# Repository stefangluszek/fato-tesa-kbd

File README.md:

# Fat-o-tesa - v0.2

## Introduction
This repository documents my attempt at building a custom mechanical keyboard. I have been considering switching to a split ergonomic keyboard such as the [Ergodox](https://ergodox-ez.com/) for a while now.
I hesitated, mostly because I love my current Varmillo Mechanical keyboard and I was not sure if switching back and forth between the two would be a good idea. At the end I decided it was more about learning the process of building a custom keyboard than actually using it. So I decided to design and build my own custom mechanical keyboard.

The requirements I had were simple, a split mechanical keyboard with the base layout as close to the ISO layout as possible to make switching back and forth as painless as possible. Why ISO? Because I use a Swedish/Norwegian keyboard which uses the ISO layout.

## The layout
I used the [Keyboard Layout Editor](http://www.keyboard-layout-editor.com/) to create the layout. It's based on the ISO 60% preset, but includes the top row with a couple of functional keys. I will explain why I needed the top row later on when we get to the PCB design.

The raw layout can be found [here](layouts/layout.kle).

## version v0.2
This is my second attempt at designing the PCBs. The [first version](README.v0.1.md) was a good learning experience but it had some major flaws that are addressed in this version.

## PCB design
The PCB is designed in KiCAD 7. The schematics are improved compared to v0.1. I grouped things together by function and made sure all symbols are consistent and match the PCB. I have also made sure to have all the footprint libraries available.

The PCB routing and component placement is also improved. All signal traces are routed on the bottom layer and the top layer is used as a ground layer. Since this is a keyboard matrix, I had to use some vias to jump over the vertical traces when routing the horizontal ones. An alternative, which most other keyboards seem to go for, is to route columns on the top and rows on the bottom layer. The wiring would be cleaner but you end up cutting the ground plane with long traces across the entire PCB, which according to [Rick Hartley](https://www.youtube.com/watch?v=ySuUZEjARPY) is not good. It probably doesn't matter for simple passive switches but I have the IC2 for the RGB LEDs so I thought, what the heck, let's try that. Another alternative was a 4 layer board, with signals on top and bottom with ground on the middle layers. 4 layer PCBs are more expensive, and since I don't believe this to be the final prototype, I decided to stick with 2 layers. Also, I've decided to order left and right PCBs separately. This way I can learn for half the cost. I made sure to have all 3D models available to make sure I didn't end up with any overlapping components like I did in v0.1.

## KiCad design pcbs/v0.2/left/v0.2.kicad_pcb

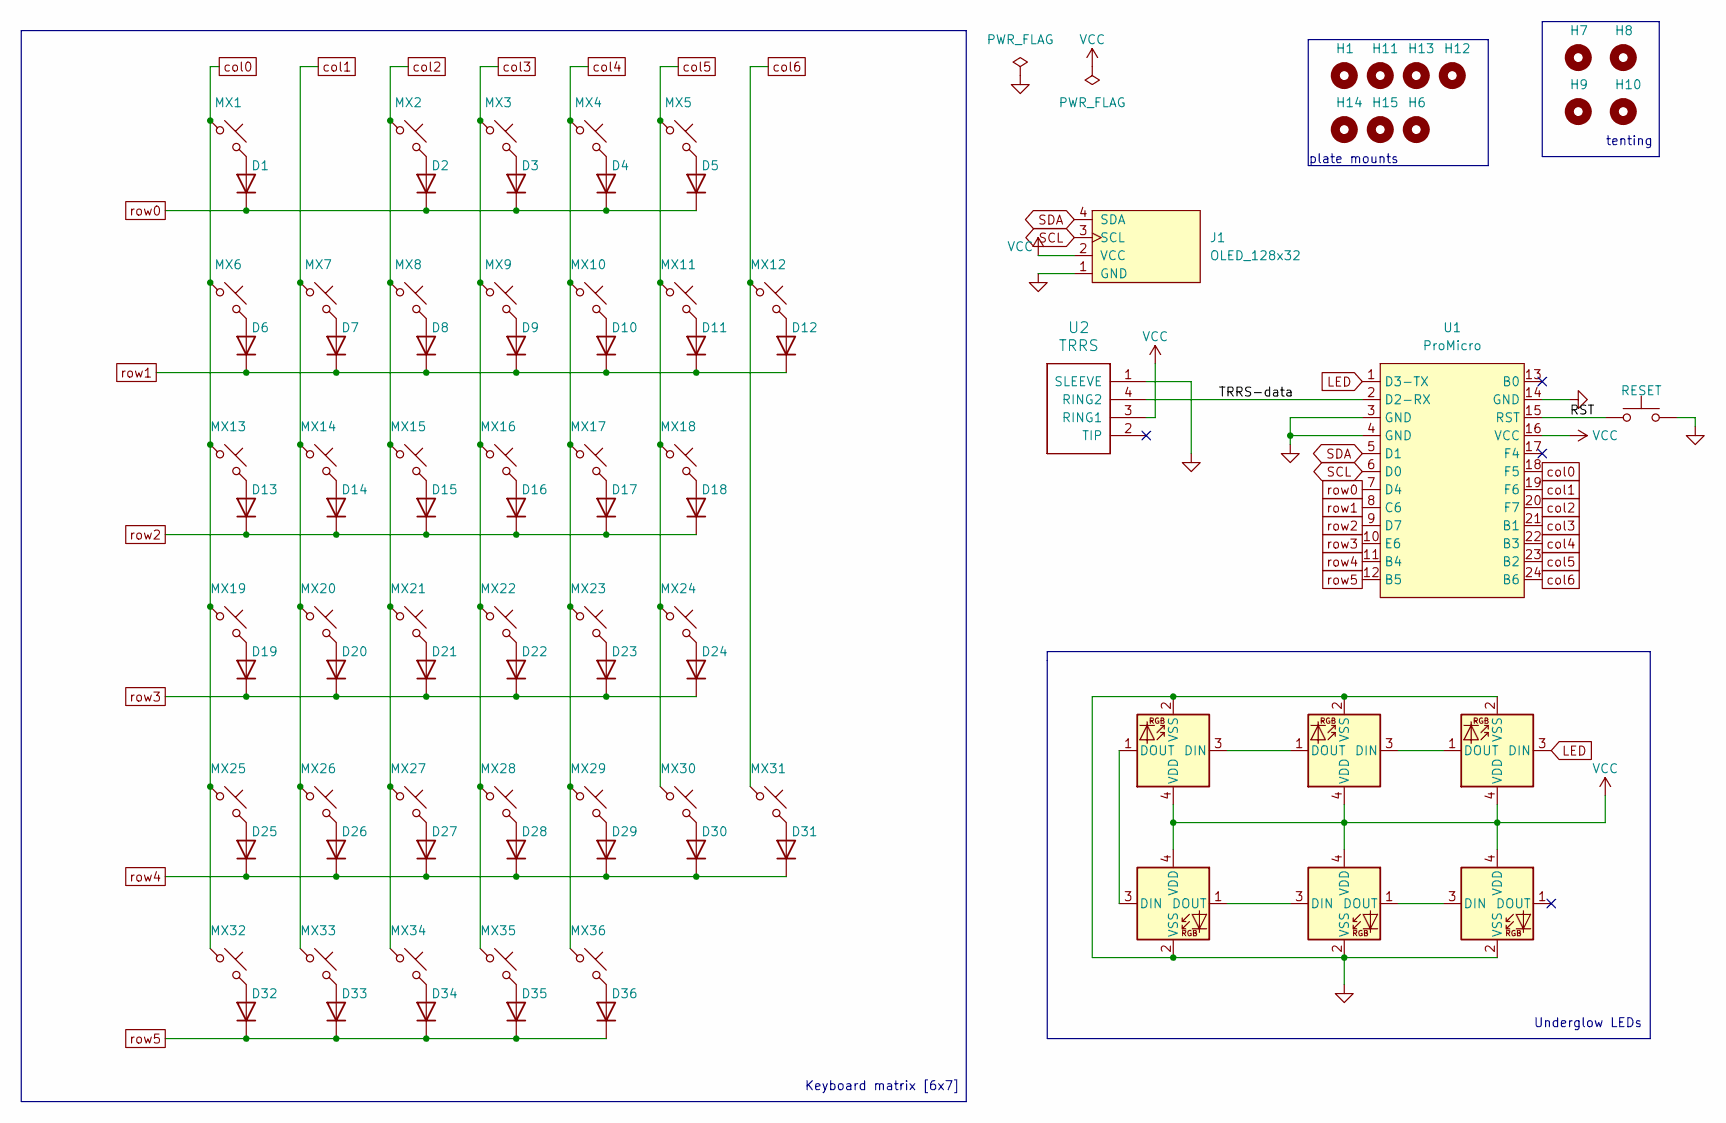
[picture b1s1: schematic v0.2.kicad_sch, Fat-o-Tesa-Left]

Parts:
D1, D2, D3, D4, D5, D6, D7, D8, D9, D10, D11, D12, D13, D14, D15, D16, D17, D18, D19, D20, D21, D22, D23, D24, D25, D26, D27, D28, D29, D30, D31, D32, D33, D34, D35, D36: Diode; D_DO-35_SOD27_P7.62mm_Horizontal
D37, D38, D39, D40, D41, D42: SK6812MINI; LED_SK6812MINI_PLCC4_3.5x3.5mm_P1.75mm
H1, H6, H11, H12, H13, H14, H15: MountingHole; MountingHole_4.3mm_M4
H7, H8, H9, H10: MountingHole; MountingHole_5.3mm_M5
J1: OLED_128x32
MX1, MX2, MX3, MX4, MX5, MX6, MX7, MX8, MX9, MX10, MX11, MX12, MX14, MX15, MX16, MX17, MX18, MX20, MX21, MX22, MX23, MX24, MX26, MX27, MX28, MX29, MX30, MX31, MX36: MX_SW_HS; MX_PCB_1.00u
MX13: MX_SW_HS; MX_PCB_1.50u
MX19, MX35: MX_SW_HS; MX_PCB_1.75u
MX25, MX32, MX33, MX34: MX_SW_HS; MX_PCB_1.25u
SW2: RESET; ResetSMD_SG
U1: ProMicro; ProMicro_Reversible_Single
U2: TRRS; TRRS_PJ-320A

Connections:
/RST: SW2.1, U1.15 (RST)
/TRRS-data: U1.2 (D2-RX), U2.4 (RING2)
GND: D37.2 (VSS), D38.2 (VSS), D39.2 (VSS), D40.2 (VSS), D41.2 (VSS), D42.2 (VSS), J1.1 (GND), SW2.2, U1.3 (GND), U1.4 (GND), U1.14 (GND), U2.1 (SLEEVE)
LED: D37.3 (DIN), U1.1 (D3-TX)
unnamed: D1.2 (A), MX1.2
unnamed: D2.2 (A), MX2.2
unnamed: D3.2 (A), MX3.2
unnamed: D4.2 (A), MX4.2
unnamed: D5.2 (A), MX5.2
unnamed: D6.2 (A), MX6.2
unnamed: D7.2 (A), MX7.2
unnamed: D8.2 (A), MX8.2
unnamed: D9.2 (A), MX9.2
unnamed: D10.2 (A), MX10.2
unnamed: D11.2 (A), MX11.2
unnamed: D12.2 (A), MX12.2
unnamed: D13.2 (A), MX13.2
unnamed: D14.2 (A), MX14.2
unnamed: D15.2 (A), MX15.2
unnamed: D16.2 (A), MX16.2
unnamed: D17.2 (A), MX17.2
unnamed: D18.2 (A), MX18.2
unnamed: D19.2 (A), MX19.2
unnamed: D20.2 (A), MX20.2
unnamed: D21.2 (A), MX21.2
unnamed: D22.2 (A), MX22.2
unnamed: D23.2 (A), MX23.2
unnamed: D24.2 (A), MX24.2
unnamed: D25.2 (A), MX25.2
unnamed: D26.2 (A), MX26.2
unnamed: D27.2 (A), MX27.2
unnamed: D28.2 (A), MX28.2
unnamed: D29.2 (A), MX29.2
unnamed: D30.2 (A), MX30.2
unnamed: D31.2 (A), MX31.2
unnamed: D32.2 (A), MX32.2
unnamed: D33.2 (A), MX33.2
unnamed: D34.2 (A), MX34.2
unnamed: D35.2 (A), MX35.2
unnamed: D36.2 (A), MX36.2
unnamed: D37.1 (DOUT), D38.3 (DIN)
unnamed: D38.1 (DOUT), D39.3 (DIN)
unnamed: D39.1 (DOUT), D40.3 (DIN)
unnamed: D40.1 (DOUT), D41.3 (DIN)
unnamed: D41.1 (DOUT), D42.3 (DIN)
SCL: J1.3 (SCL), U1.6 (D0)
SDA: J1.4 (SDA), U1.5 (D1)
VCC: D37.4 (VDD), D38.4 (VDD), D39.4 (VDD), D40.4 (VDD), D41.4 (VDD), D42.4 (VDD), J1.2 (VCC), U1.16 (VCC), U2.3 (RING1)
col0: MX1.1, MX6.1, MX13.1, MX19.1, MX25.1, MX32.1, U1.18 (F5)
col1: MX7.1, MX14.1, MX20.1, MX26.1, MX33.1, U1.19 (F6)
col2: MX2.1, MX8.1, MX15.1, MX21.1, MX27.1, MX34.1, U1.20 (F7)
col3: MX3.1, MX9.1, MX16.1, MX22.1, MX28.1, MX35.1, U1.21 (B1)
col4: MX4.1, MX10.1, MX17.1, MX23.1, MX29.1, MX36.1, U1.22 (B3)
col5: MX5.1, MX11.1, MX18.1, MX24.1, MX30.1, U1.23 (B2)
col6: MX12.1, MX31.1, U1.24 (B6)
row0: D1.1 (K), D2.1 (K), D3.1 (K), D4.1 (K), D5.1 (K), U1.7 (D4)
row1: D6.1 (K), D7.1 (K), D8.1 (K), D9.1 (K), D10.1 (K), D11.1 (K), D12.1 (K), U1.8 (C6)
row2: D13.1 (K), D14.1 (K), D15.1 (K), D16.1 (K), D17.1 (K), D18.1 (K), U1.9 (D7)
row3: D19.1 (K), D20.1 (K), D21.1 (K), D22.1 (K), D23.1 (K), D24.1 (K), U1.10 (E6)
row4: D25.1 (K), D26.1 (K), D27.1 (K), D28.1 (K), D29.1 (K), D30.1 (K), D31.1 (K), U1.11 (B4)
row5: D32.1 (K), D33.1 (K), D34.1 (K), D35.1 (K), D36.1 (K), U1.12 (B5)

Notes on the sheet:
tenting
plate mounts
Keyboard matrix [6x7]
Underglow LEDs

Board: 2 copper layers, 93 parts (43 on the bottom side), 61 nets, no tracks yet.

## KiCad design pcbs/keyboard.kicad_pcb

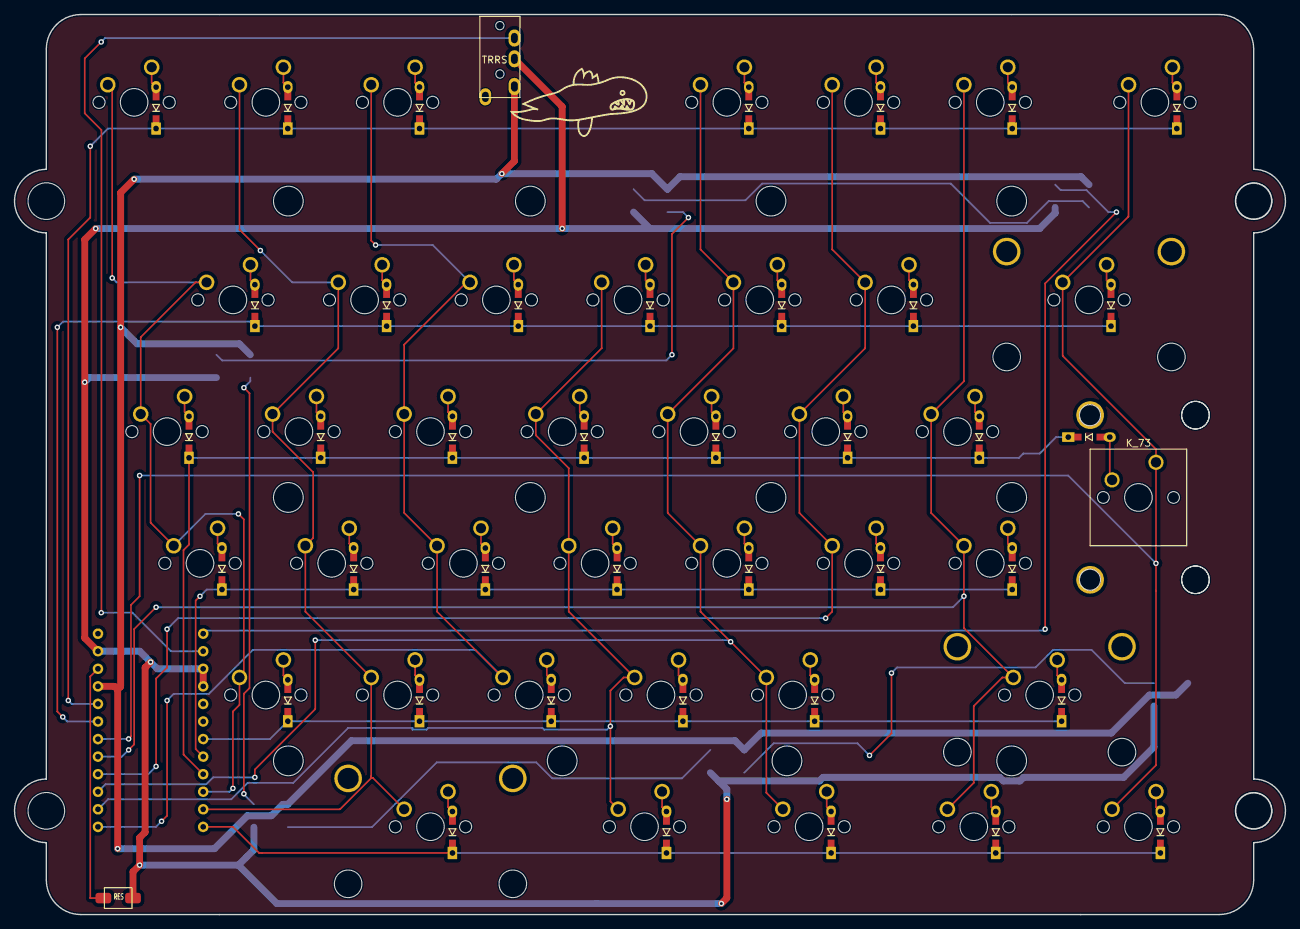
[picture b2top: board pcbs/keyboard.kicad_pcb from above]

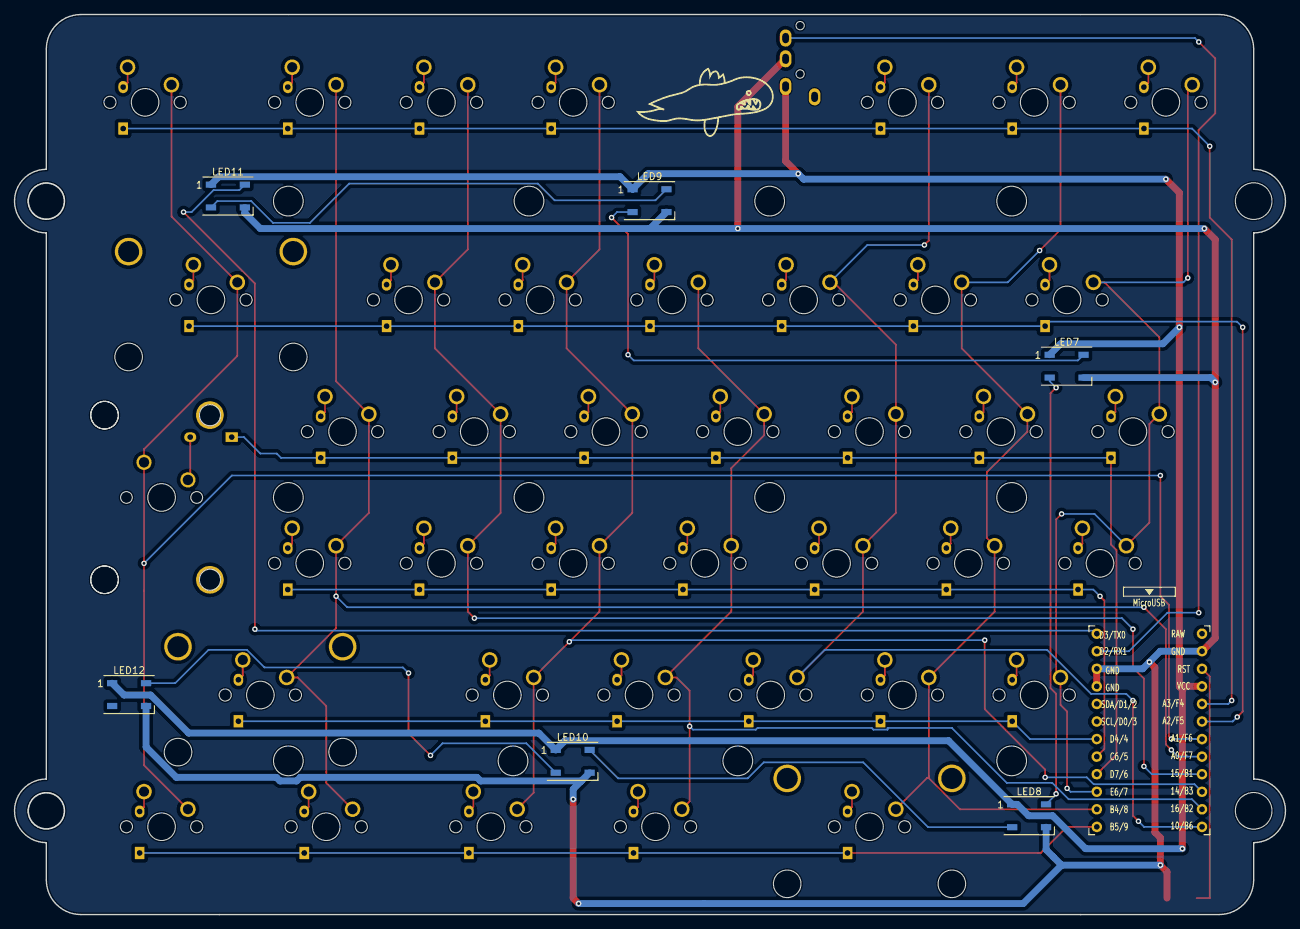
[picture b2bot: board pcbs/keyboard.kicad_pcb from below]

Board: 2 copper layers, 183.8 x 130.2 mm, 109 parts (7 on the bottom side), 64 nets.

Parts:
D_35, D_36, D_37, D_38, D_39, D_40, D_41, D_42, D_43, D_44, D_45, D_46, D_47, D_48, D_49, D_50, D_51, D_52, D_53, D_54, D_55, D_56, D_57, D_58, D_59, D_60, D_61, D_62, D_63, D_64, D_65, D_66, D_67, D_68, D_69, D_70, D_71, D_72, D_73, D_74: D; D3_TH
H13, H14, H15, H16, H17, H18, H19, H20, H21, H22, H23, H24: MountingHole; MountingHole_4.3mm_M4
H28, H29, H30, H32: MountingHole; MountingHole_5.3mm_M5
J2: MJ-4PP-9; MJ-4PP-9_1side
K_35, K_36, K_37, K_38, K_39, K_40, K_41, K_42, K_43, K_44, K_45, K_46, K_47, K_48, K_49, K_50, K_51, K_52, K_53, K_54, K_55, K_57, K_58, K_59, K_60, K_61, K_63, K_64, K_65, K_66, K_68, K_69, K_70, K_71, K_72: KEYSW; MXOnly-1U-NoLED
K_56, K_62, K_67, K_74: KEYSW; MXOnly-1.25U-NoLED
K_73: KEYSW; SW_Cherry_MX_ISOEnter_PCB
LED7, LED8, LED9, LED10, LED11, LED12: WS2812B; LED_WS2812B_PLCC4_5.0x5.0mm_P3.2mm
S1, S3, S4: MX_stab; STAB_MX_P_2u
S2: MX_stab; STAB_MX_P_2.75u
SW2: SW_PUSH; ResetSMD_SG
U1: ProMicro; ProMicro_v3_inverted

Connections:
GNDA: J2.C, LED7.3 (VSS), LED8.3 (VSS), LED9.3 (VSS), LED10.3 (VSS), LED11.3 (VSS), LED12.3 (VSS), SW2.2, U1.3 (GND), U1.4 (GND), U1.23 (GND)
LED_r: LED11.4 (DIN), U1.1 (TX0/D3)
unnamed: D_35.2 (A), K_35.2 (ROW)
unnamed: D_36.2 (A), K_36.2 (ROW)
unnamed: D_37.2 (A), K_37.2 (ROW)
unnamed: D_38.2 (A), K_38.2 (ROW)
unnamed: D_39.2 (A), K_39.2 (ROW)
unnamed: D_40.2 (A), K_40.2 (ROW)
unnamed: D_41.2 (A), K_41.2 (ROW)
unnamed: D_42.2 (A), K_42.2 (ROW)
unnamed: D_43.2 (A), K_43.2 (ROW)
unnamed: D_44.2 (A), K_44.2 (ROW)
unnamed: D_45.2 (A), K_45.2 (ROW)
unnamed: D_46.2 (A), K_46.2 (ROW)
unnamed: D_47.2 (A), K_47.2 (ROW)
unnamed: D_48.2 (A), K_48.2 (ROW)
unnamed: D_49.2 (A), K_49.2 (ROW)
unnamed: D_50.2 (A), K_50.2 (ROW)
unnamed: D_51.2 (A), K_51.2 (ROW)
unnamed: D_52.2 (A), K_52.2 (ROW)
unnamed: D_53.2 (A), K_53.2 (ROW)
unnamed: D_54.2 (A), K_54.2 (ROW)
unnamed: D_55.2 (A), K_55.2 (ROW)
unnamed: D_56.2 (A), K_56.2 (ROW)
unnamed: D_57.2 (A), K_57.2 (ROW)
unnamed: D_58.2 (A), K_58.2 (ROW)
unnamed: D_59.2 (A), K_59.2 (ROW)
unnamed: D_60.2 (A), K_60.2 (ROW)
unnamed: D_61.2 (A), K_61.2 (ROW)
unnamed: D_62.2 (A), K_62.2 (ROW)
unnamed: D_63.2 (A), K_63.2 (ROW)
unnamed: D_64.2 (A), K_64.2 (ROW)
unnamed: D_65.2 (A), K_65.2 (ROW)
unnamed: D_66.2 (A), K_66.2 (ROW)
unnamed: D_67.2 (A), K_67.2 (ROW)
unnamed: D_68.2 (A), K_68.2 (ROW)
unnamed: D_69.2 (A), K_69.2 (ROW)
unnamed: D_70.2 (A), K_70.2 (ROW)
unnamed: D_71.2 (A), K_71.2 (ROW)
unnamed: D_72.2 (A), K_72.2 (ROW)
unnamed: D_73.2 (A), K_73.2 (ROW)
unnamed: D_74.2 (A), K_74.2 (ROW)
unnamed: LED7.4 (DIN), LED9.2 (DOUT)
unnamed: LED7.2 (DOUT), LED8.4 (DIN)
unnamed: LED8.2 (DOUT), LED10.4 (DIN)
unnamed: LED10.2 (DOUT), LED12.4 (DIN)
unnamed: LED9.4 (DIN), LED11.2 (DOUT)
VDD: J2.D, LED7.1 (VDD), LED8.1 (VDD), LED9.1 (VDD), LED10.1 (VDD), LED11.1 (VDD), LED12.1 (VDD), U1.21 (VCC)
col0_r: K_35.1 (COL), K_36.1 (COL), K_38.1 (COL), K_40.1 (COL), K_41.1 (COL), U1.10 (7/E6)
col1_r: K_37.1 (COL), K_39.1 (COL), K_43.1 (COL), K_45.1 (COL), K_46.1 (COL), K_47.1 (COL), U1.11 (8/B4)
col2_r: K_42.1 (COL), K_44.1 (COL), K_48.1 (COL), K_50.1 (COL), K_51.1 (COL), U1.13 (B6/10)
col3_r: K_49.1 (COL), K_52.1 (COL), K_54.1 (COL), K_55.1 (COL), K_56.1 (COL), U1.14 (B2/16)
col4_r: K_53.1 (COL), K_57.1 (COL), K_58.1 (COL), K_60.1 (COL), K_61.1 (COL), K_62.1 (COL), U1.15 (B3/14)
col5_r: K_59.1 (COL), K_63.1 (COL), K_64.1 (COL), K_66.1 (COL), U1.16 (B1/15)
col6_r: K_65.1 (COL), K_67.1 (COL), K_68.1 (COL), K_70.1 (COL), K_71.1 (COL), U1.17 (F7/A0)
col7_r: K_69.1 (COL), K_72.1 (COL), K_73.1 (COL), K_74.1 (COL), U1.18 (F6/A1)
data_r: J2.B, U1.2 (RX1/D2)
reset_r: SW2.1, U1.22 (RST)
row0_r: D_35.1 (K), D_37.1 (K), D_42.1 (K), D_57.1 (K), D_63.1 (K), D_68.1 (K), D_72.1 (K), U1.20 (F4/A3)
row1_r: D_38.1 (K), D_43.1 (K), D_48.1 (K), D_52.1 (K), D_58.1 (K), D_64.1 (K), D_69.1 (K), U1.19 (F5/A2)
row2_r: D_36.1 (K), D_39.1 (K), D_44.1 (K), D_49.1 (K), D_53.1 (K), D_59.1 (K), D_65.1 (K), D_73.1 (K), U1.9 (6/D7)
row3_r: D_40.1 (K), D_45.1 (K), D_50.1 (K), D_54.1 (K), D_60.1 (K), D_66.1 (K), D_70.1 (K), U1.8 (5/C6)
row4_r: D_41.1 (K), D_46.1 (K), D_51.1 (K), D_55.1 (K), D_61.1 (K), D_71.1 (K), U1.7 (4/D4)
row5_r: D_47.1 (K), D_56.1 (K), D_62.1 (K), D_67.1 (K), D_74.1 (K), U1.12 (9/B5)

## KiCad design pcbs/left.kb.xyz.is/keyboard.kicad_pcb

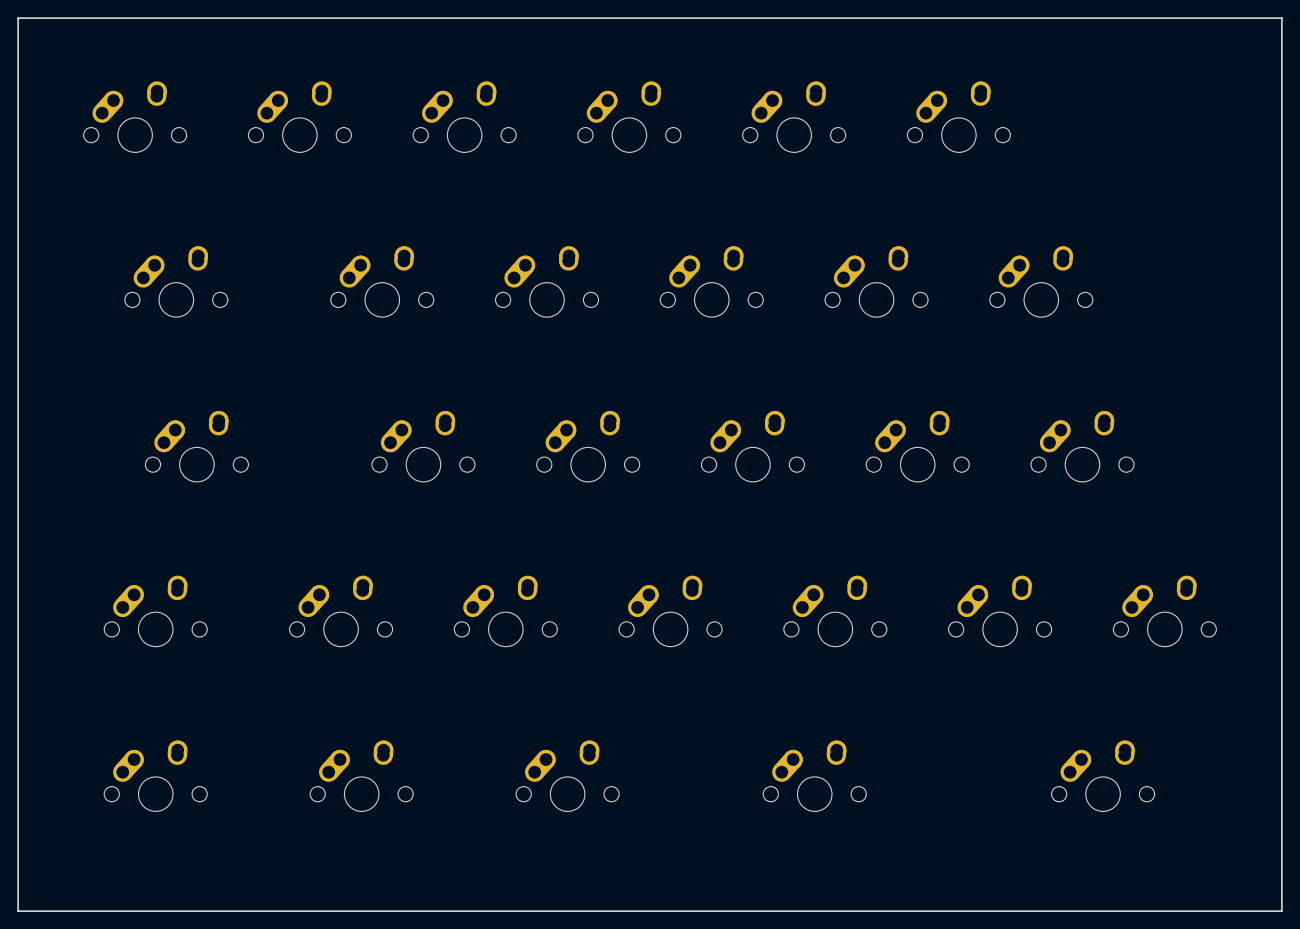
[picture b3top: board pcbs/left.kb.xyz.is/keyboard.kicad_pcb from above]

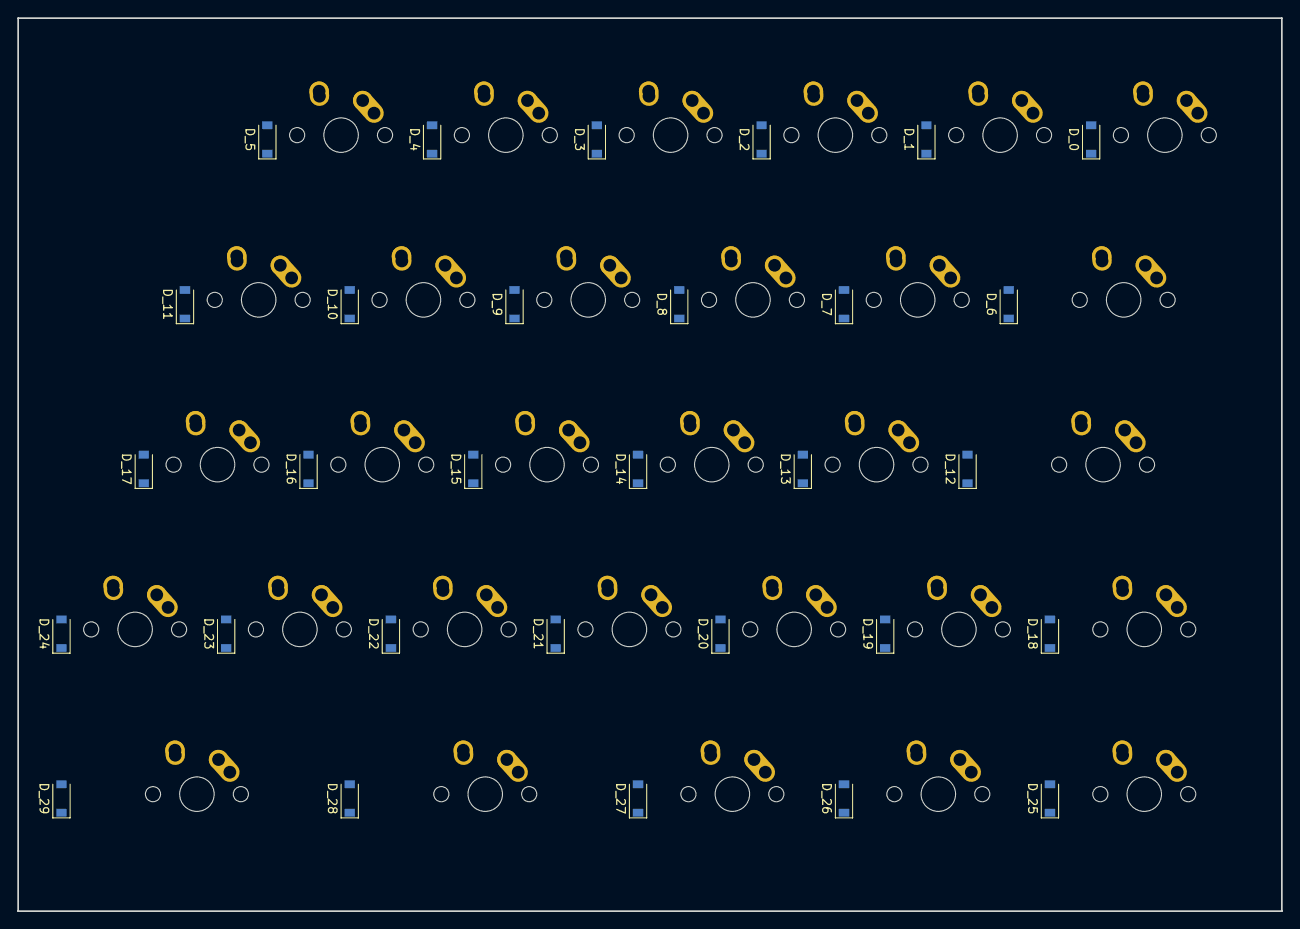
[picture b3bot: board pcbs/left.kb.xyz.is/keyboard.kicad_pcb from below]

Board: 2 copper layers, 146.1 x 103.2 mm, 60 parts (30 on the bottom side), 42 nets, no tracks yet.

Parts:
D_0, D_1, D_2, D_3, D_4, D_5, D_6, D_7, D_8, D_9, D_10, D_11, D_12, D_13, D_14, D_15, D_16, D_17, D_18, D_19, D_20, D_21, D_22, D_23, D_24, D_25, D_26, D_27, D_28, D_29: D; D_SOD-123
K_0, K_1, K_2, K_3, K_4, K_5, K_7, K_8, K_9, K_10, K_11, K_13, K_14, K_15, K_16, K_17, K_19, K_20, K_21, K_22, K_23, K_24: KEYSW; MX-1U-NoLED
K_6: KEYSW; MX-1.5U-NoLED
K_12, K_28, K_29: KEYSW; MX-1.75U-NoLED
K_18, K_25, K_26, K_27: KEYSW; MX-1.25U-NoLED

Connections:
unnamed: D_0.2, K_0.2
unnamed: D_1.2, K_1.2
unnamed: D_2.2, K_2.2
unnamed: D_3.2, K_3.2
unnamed: D_4.2, K_4.2
unnamed: D_5.2, K_5.2
unnamed: D_6.2, K_6.2
unnamed: D_7.2, K_7.2
unnamed: D_8.2, K_8.2
unnamed: D_9.2, K_9.2
unnamed: D_10.2, K_10.2
unnamed: D_11.2, K_11.2
unnamed: D_12.2, K_12.2
unnamed: D_13.2, K_13.2
unnamed: D_14.2, K_14.2
unnamed: D_15.2, K_15.2
unnamed: D_16.2, K_16.2
unnamed: D_17.2, K_17.2
unnamed: D_18.2, K_18.2
unnamed: D_19.2, K_19.2
unnamed: D_20.2, K_20.2
unnamed: D_21.2, K_21.2
unnamed: D_22.2, K_22.2
unnamed: D_23.2, K_23.2
unnamed: D_24.2, K_24.2
unnamed: D_25.2, K_25.2
unnamed: D_26.2, K_26.2
unnamed: D_27.2, K_27.2
unnamed: D_28.2, K_28.2
unnamed: D_29.2, K_29.2
col0: K_0.1, K_6.1, K_12.1, K_18.1, K_25.1
col1: K_1.1, K_19.1, K_26.1
col2: K_2.1, K_7.1, K_13.1, K_20.1
col3: K_3.1, K_8.1, K_14.1, K_21.1, K_27.1
col4: K_4.1, K_9.1, K_15.1, K_22.1, K_28.1
col5: K_5.1, K_10.1, K_16.1, K_23.1
col6: K_11.1, K_17.1, K_24.1, K_29.1
row0: D_0.1, D_1.1, D_2.1, D_3.1, D_4.1, D_5.1
row1: D_6.1, D_7.1, D_8.1, D_9.1, D_10.1, D_11.1
row2: D_12.1, D_13.1, D_14.1, D_15.1, D_16.1, D_17.1
row3: D_18.1, D_19.1, D_20.1, D_21.1, D_22.1, D_23.1, D_24.1
row4: D_25.1, D_26.1, D_27.1, D_28.1, D_29.1

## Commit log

2023-11-21 Initial Layout and PCB
2023-11-22 Generated PCBs
2023-11-25 Fato-Tesa-Kbd - Put both boards into a single project.
2023-11-27 Update .gitignore.
2023-11-27 Updated pcbs.
2023-11-29 Use smd+through hole diode footprint.
2023-12-01 Fixed board outlines + breakout pads.
2023-12-02 Added CU fill and other stuff.
2023-12-02 Added LEDs for underglow.
2023-12-05 Updates,
    1. replaced the PCB outline with a CAD designed model
    2. Added drill holes
    3. Added mouse bites
2023-12-05 Use MX+Choc switch footprints.
2023-12-06 Wired up the left side.
2023-12-08 Some small adjustment to the layout
2023-12-09 Updated the layout.
    Use single layout for both left and right sides.
2023-12-09 Document the layout.
2023-12-10 Top plate CAD model.
2023-12-11 Use u2 for the right space and u1 for left.
    This will make they keycaps compatible with ISO 105 sets.
2023-12-17 Re-design the outline based on the PCB.
2024-01-06 Re-done traces.
    After doing some more research, I've learned that power delivery traces
    should be at least 0.5mm. I made them 1mm thick, and had to re-do all
    traces.
2024-01-06 Final touches, and the order.
2024-01-07 Branch for a split jlcpcb order.
2024-01-17 Pre-assembly!
2024-01-19 v0.1 Lessons learned.
2024-01-20 Moved v0.1 to a separate folder.
    Will keep for now for the future reference.
2024-01-20 Updated .gitignore.
2024-01-20 Removed some backups.
2024-01-20 Made some room for the controller on the right side.
2024-01-20 Updated gitignore
2024-01-21 Left side schematics.
    Unfortunately ran out of pins to have both the rotary encoder and the
    OLED.
2024-01-22 Move the rotary encoder to the right side.
    This hopefully should make pins available for the OLED on the left side.
2024-02-02 Update gitignore.
2024-02-02 Fixed typo.
2024-02-02 v0.2 - Left - PCB.
2024-02-03 Updated layout
2024-03-07 Added labels to key layout.
2024-03-10 Added labels to the right side.
2024-03-10 The birth of the right side of the v0.2
    Schematics should be complete. Next up the PCB.
2024-03-14 Layed out the switches on the PCB
2024-03-17 Updated the underglow symbols and footprints.
2024-03-17 Routed PCB traces.
2024-04-06 Added right side PCB render.
2024-04-06 Snapshot 2024-04-07
2024-04-07 No-caps finished.
2024-04-07 v0.2 - Left - Updated LEDs Symbols.
    NOTE: This caused the traces to no longer match the footprint and thus
    removed.
    MISSING TRACES!
